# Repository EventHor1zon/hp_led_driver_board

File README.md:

# hp_led_driver_board
10W RGB LED Driver &amp;Controller board

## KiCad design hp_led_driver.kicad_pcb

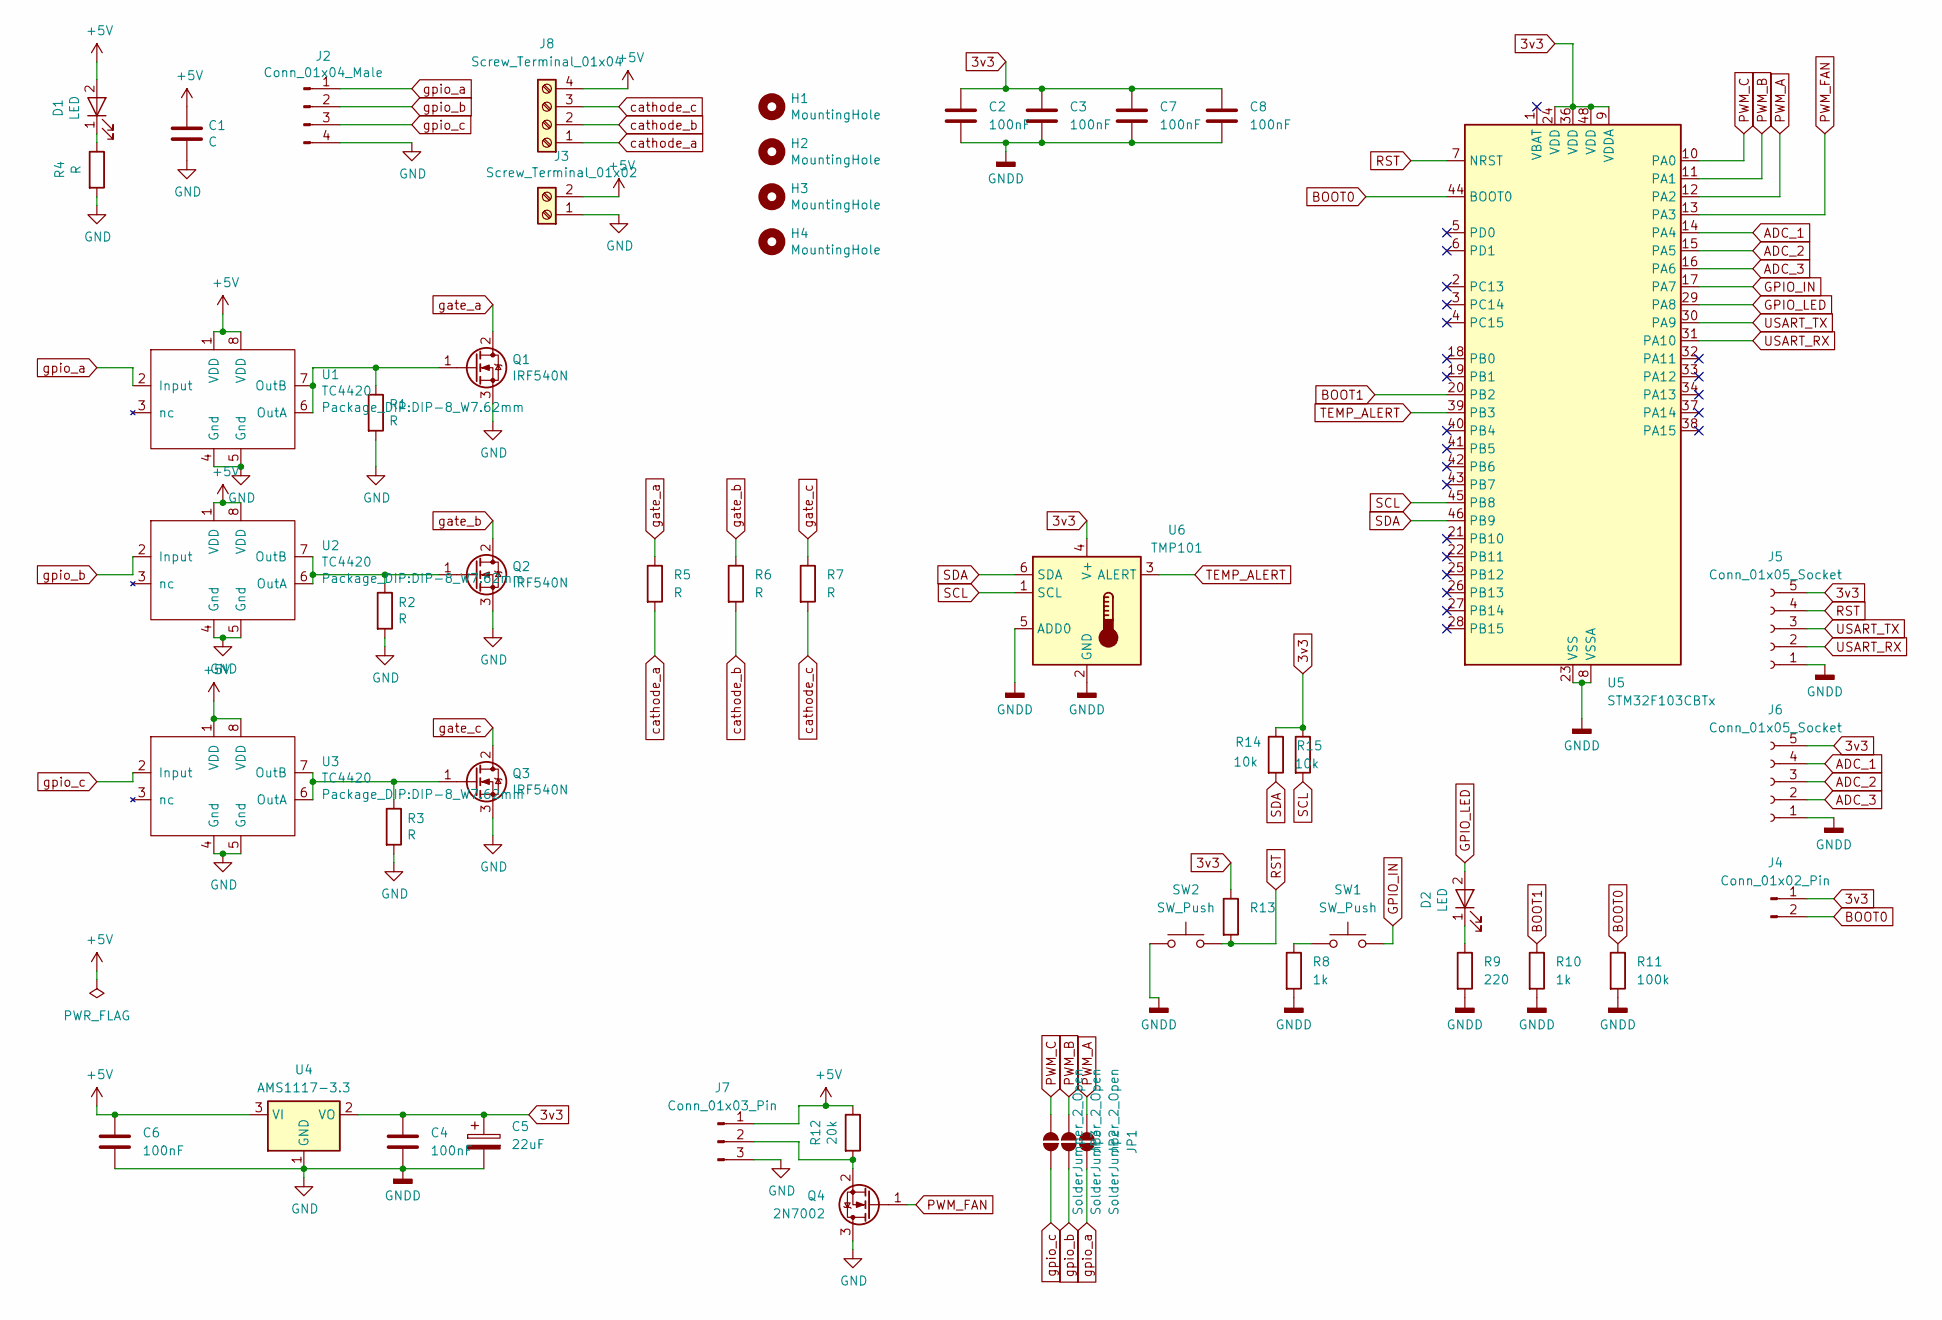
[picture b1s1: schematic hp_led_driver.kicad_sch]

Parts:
C1: C; CP_Radial_Tantal_D4.5mm_P2.50mm
C2, C3, C4, C6, C7, C8: 100nF; C_0805_2012Metric_Pad1.18x1.45mm_HandSolder
C5: 22uF; CP_Radial_Tantal_D4.5mm_P2.50mm
D1, D2: LED; LED_0805_2012Metric_Pad1.15x1.40mm_HandSolder
H1, H2, H3, H4: MountingHole; MountingHole_2.5mm_Pad
J2: Conn_01x04_Male; PinHeader_1x04_P2.54mm_Vertical
J3: Screw_Terminal_01x02; TerminalBlock_bornier-2_P5.08mm
J4: Conn_01x02_Pin; PinHeader_1x02_P2.54mm_Vertical
J5, J6: Conn_01x05_Socket; PinHeader_1x05_P2.54mm_Vertical
J7: Conn_01x03_Pin; PinHeader_1x03_P2.54mm_Vertical
J8: Screw_Terminal_01x04; TerminalBlock_bornier-4_P5.08mm
JP1, JP2, JP3: SolderJumper_2_Open; SolderJumper-2_P1.3mm_Open_TrianglePad1.0x1.5mm
Q1, Q2, Q3: IRF540N; TO-220-3_Vertical
Q4: 2N7002; SOT-23
R1, R2, R3: R; R_Axial_DIN0207_L6.3mm_D2.5mm_P7.62mm_Horizontal
R4: R; R_0805_2012Metric
R5, R6, R7: R; R_Axial_Power_L25.0mm_W6.4mm_P30.48mm
R8, R10: 1k; R_0805_2012Metric
R9: 220; R_0805_2012Metric
R11: 100k; R_0805_2012Metric
R12: 20k; R_0805_2012Metric
R13, R14, R15: 10k; R_0805_2012Metric
SW1, SW2: SW_Push; SW_PUSH_6mm
U1, U2, U3: TC4420; DIP-8_W7.62mm
U4: AMS1117-3.3; SOT-223-3_TabPin2
U5: STM32F103CBTx; LQFP-48_7x7mm_P0.5mm
U6: TMP101; SOT-23-6

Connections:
3v3: C2.1, C3.1, C4.1, C5.1, C7.1, C8.1, J4.1, J5.5, J6.5, R13.1, R14.1, R15.1, U4.2 (VO), U5.9 (VDDA), U5.24 (VDD), U5.36 (VDD), U5.48 (VDD), U6.4 (V+); also elsewhere on the board
+5V: C1.1, C6.1, D1.2 (A), J3.2, J7.1, J8.4, R12.1, U1.1 (VDD), U1.8 (VDD), U2.1 (VDD), U2.8 (VDD), U3.1 (VDD), U3.8 (VDD), U4.3 (VI)
ADC_1: J6.4, U5.14 (PA4)
ADC_2: J6.3, U5.15 (PA5)
ADC_3: J6.2, U5.16 (PA6)
BOOT0: J4.2, R11.1, U5.44 (BOOT0); also elsewhere on the board
BOOT1: R10.1, U5.20 (PB2)
GND: C1.2, C2.2, C3.2, C4.2, C5.2, C6.2, C7.2, C8.2, J2.4, J3.1, J5.1, J6.1, J7.3, Q1.3 (S), Q2.3 (S), Q3.3 (S), Q4.3 (D), R1.2, R2.2, R3.2, R4.2, R8.2, R9.2, R10.2, R11.2, SW2.1, U1.4 (Gnd), U1.5 (Gnd), U2.4 (Gnd), U2.5 (Gnd), U3.4 (Gnd), U3.5 (Gnd), U4.1 (GND), U5.8 (VSSA), U5.23 (VSS), U5.35 (VSS), U5.47 (VSS), U6.2 (GND), U6.5 (ADD0); also elsewhere on the board
GPIO_IN: SW1.2, U5.17 (PA7); also elsewhere on the board
GPIO_LED: D2.2 (A), U5.29 (PA8); also elsewhere on the board
unnamed: D1.1 (K), R4.1
unnamed 11: D2.1 (K), R9.1; also elsewhere on the board
unnamed: J7.2, Q4.2 (S), R12.2
unnamed: Q1.1 (G), R1.1, U1.6 (OutA), U1.7 (OutB)
unnamed: Q2.1 (G), R2.1, U2.6 (OutA), U2.7 (OutB)
unnamed: Q3.1 (G), R3.1, U3.6 (OutA), U3.7 (OutB)
unnamed 16: R8.1, SW1.1; also elsewhere on the board
PWM_A: JP1.1 (A), U5.12 (PA2)
PWM_B: JP2.1 (A), U5.11 (PA1)
PWM_C: JP3.1 (A), U5.10 (PA0)
PWM_FAN: Q4.1 (G), U5.13 (PA3)
RST: J5.4, R13.2, SW2.2, U5.7 (NRST); also elsewhere on the board
SCL: R15.2, U5.45 (PB8), U6.1 (SCL)
SDA: R14.2, U5.46 (PB9), U6.6 (SDA)
TEMP_ALERT: U5.39 (PB3), U6.3 (ALERT)
USART_RX: J5.2, U5.31 (PA10)
USART_TX: J5.3, U5.30 (PA9)
cathode_a: J8.1, R5.2
cathode_b: J8.2, R6.2
cathode_c: J8.3, R7.2
gate_a: Q1.2 (D), R5.1
gate_b: Q2.2 (D), R6.1
gate_c: Q3.2 (D), R7.1
gpio_a: J2.1, JP1.2 (B), U1.2 (Input)
gpio_b: J2.2, JP2.2 (B), U2.2 (Input)
gpio_c: J2.3, JP3.2 (B), U3.2 (Input)

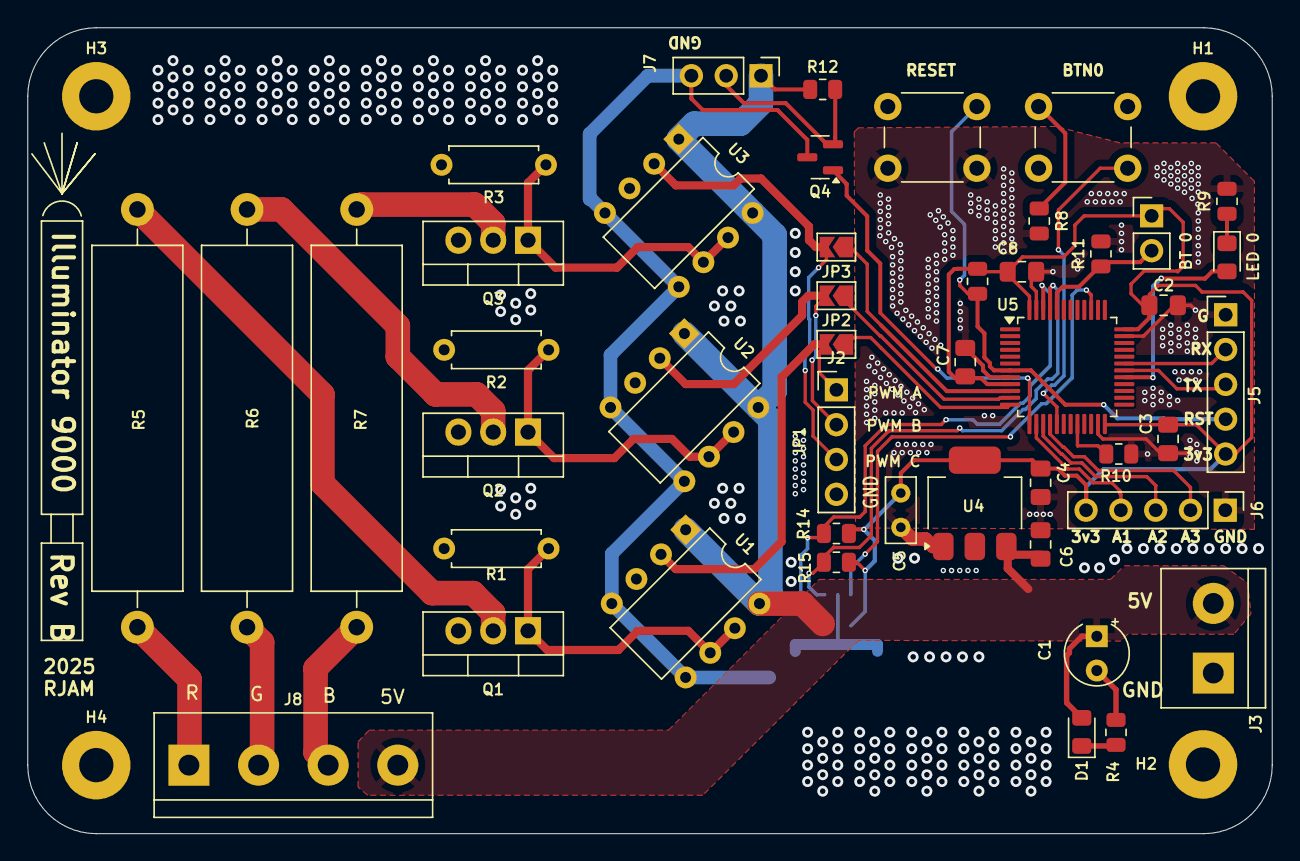
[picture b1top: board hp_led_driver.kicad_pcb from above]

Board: 2 copper layers, 90.8 x 58.8 mm, 51 parts (1 on the bottom side), 36 nets.

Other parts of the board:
BT 0: Conn_01x02_Pin; PinHeader_1x02_P2.54mm_Vertical
BTN0: SW_Push; SW_PUSH_6mm
LED 0: LED; LED_0805_2012Metric_Pad1.15x1.40mm_HandSolder
RESET: SW_Push; SW_PUSH_6mm

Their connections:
3v3: BT 0.1; also elsewhere on the board
BOOT0: BT 0.2; also elsewhere on the board
GND: RESET.1; also elsewhere on the board
GPIO_IN: BTN0.2; also elsewhere on the board
GPIO_LED: LED 0.2 (A); also elsewhere on the board
unnamed 11: LED 0.1 (K); also elsewhere on the board
unnamed 16: BTN0.1; also elsewhere on the board
RST: RESET.2; also elsewhere on the board

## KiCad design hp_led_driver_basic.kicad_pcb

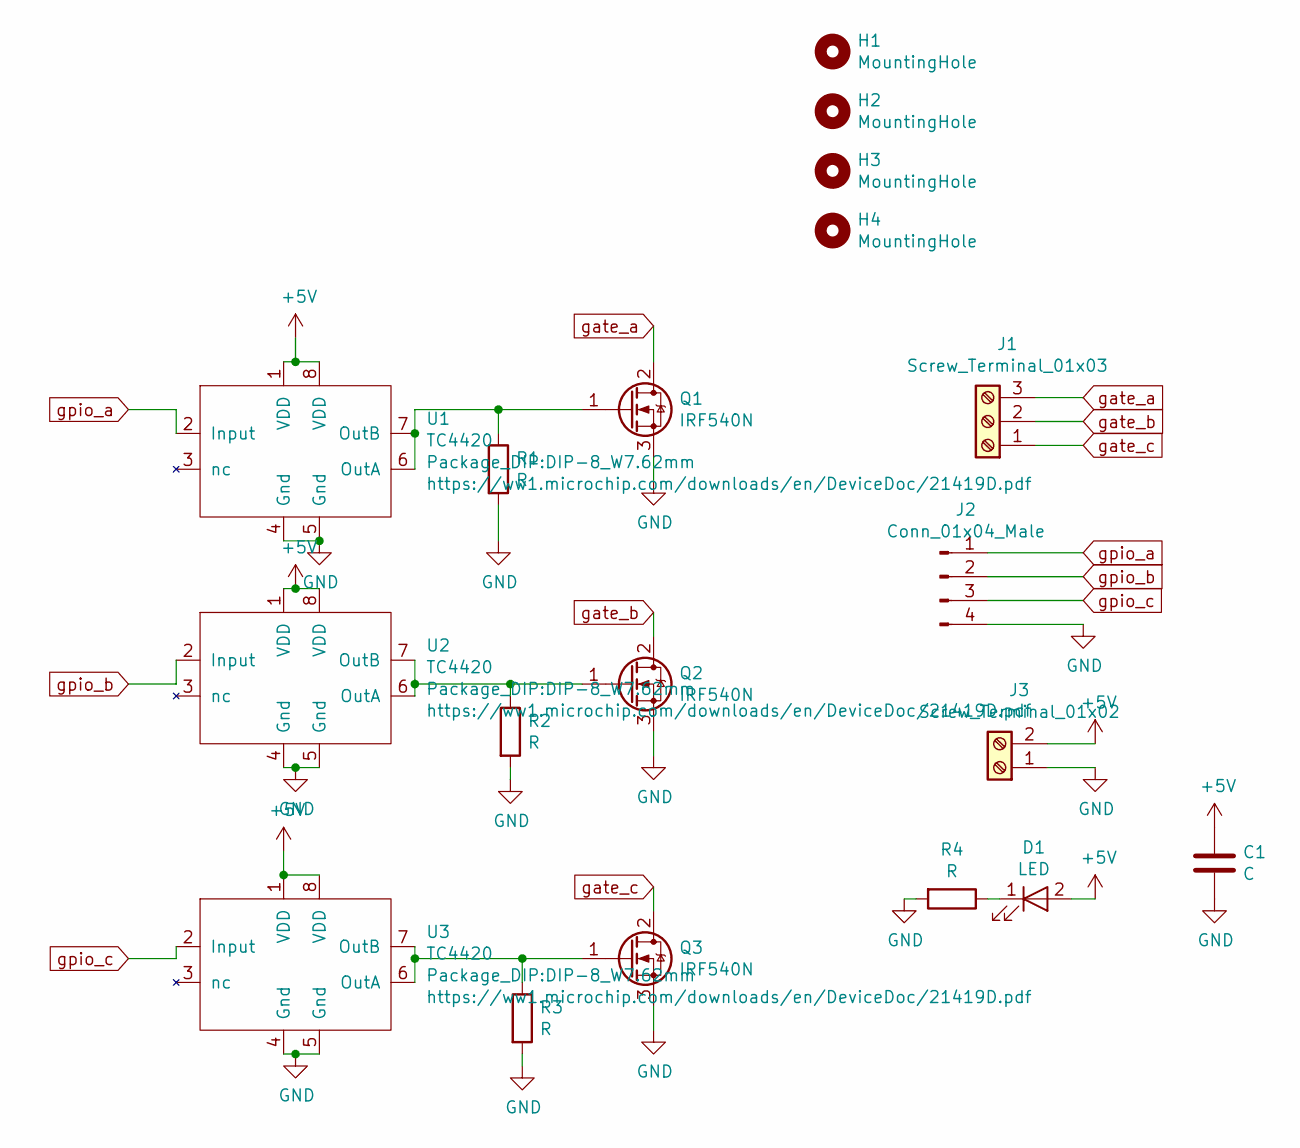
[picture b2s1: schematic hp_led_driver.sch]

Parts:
C1: C; C_Disc_D4.7mm_W2.5mm_P5.00mm
D1: LED; LED_1206_3216Metric
H1, H2, H3, H4: MountingHole; MountingHole_2.5mm_Pad
J1: Screw_Terminal_01x03; TerminalBlock_bornier-3_P5.08mm
J2: Conn_01x04_Male; PinHeader_1x04_P2.54mm_Vertical
J3: Screw_Terminal_01x02; TerminalBlock_bornier-2_P5.08mm
Q1, Q2, Q3: IRF540N; TO-220-3_Vertical
R1, R2, R3, R4: R; R_Axial_DIN0207_L6.3mm_D2.5mm_P7.62mm_Horizontal
U1, U2, U3: TC4420; DIP-8_W7.62mm

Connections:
+5V: C1.1, D1.2 (A), J3.2, U1.1 (VDD), U1.8 (VDD), U2.1 (VDD), U2.8 (VDD), U3.1 (VDD), U3.8 (VDD)
GND: C1.2, J2.4, J3.1, Q1.3 (S), Q2.3 (S), Q3.3 (S), R1.2, R2.2, R3.2, R4.2, U1.4 (Gnd), U1.5 (Gnd), U2.4 (Gnd), U2.5 (Gnd), U3.4 (Gnd), U3.5 (Gnd)
unnamed: D1.1 (K), R4.1
unnamed: Q1.1 (G), R1.1, U1.6 (OutA), U1.7 (OutB)
unnamed: Q2.1 (G), R2.1, U2.6 (OutA), U2.7 (OutB)
unnamed: Q3.1 (G), R3.1, U3.6 (OutA), U3.7 (OutB)
gate_a: J1.3, Q1.2 (D)
gate_b: J1.2, Q2.2 (D)
gate_c: J1.1, Q3.2 (D)
gpio_a: J2.1, U1.2 (Input)
gpio_b: J2.2, U2.2 (Input)
gpio_c: J2.3, U3.2 (Input)

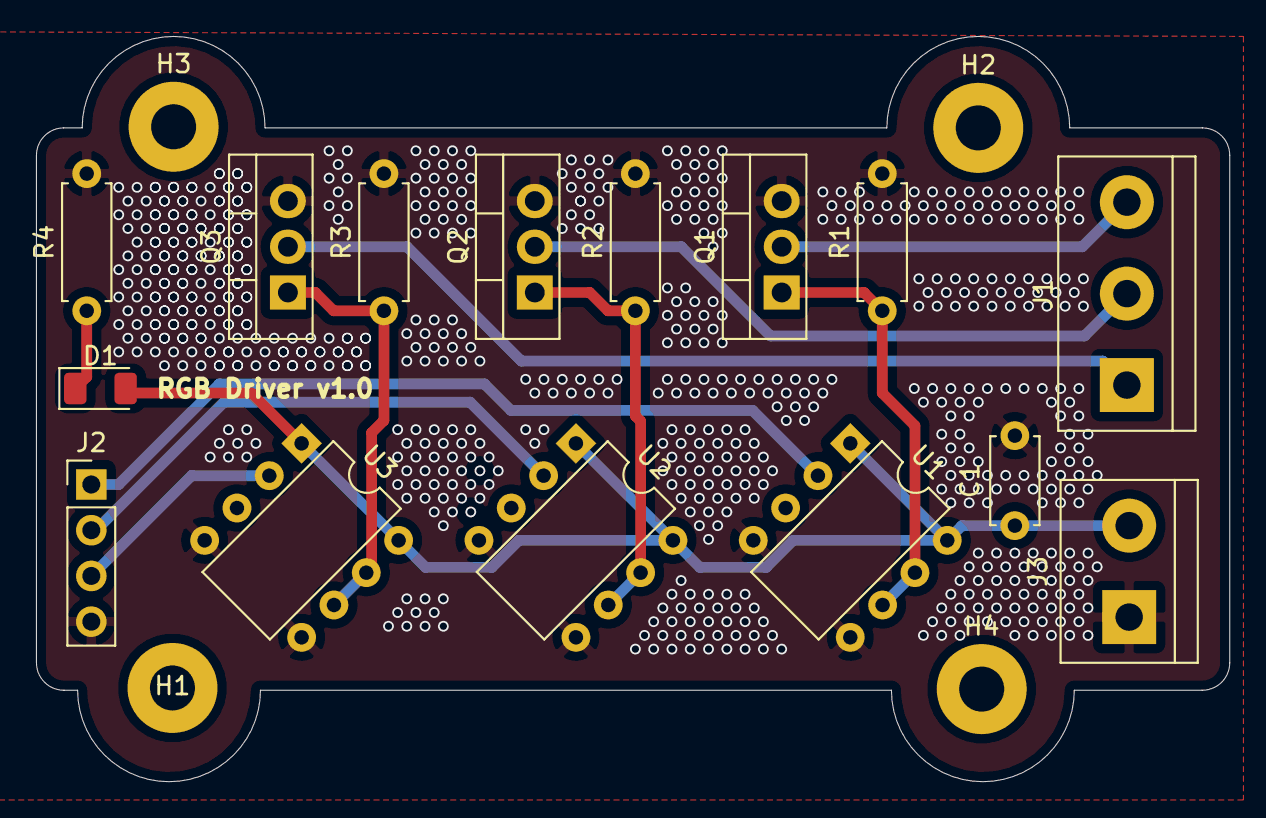
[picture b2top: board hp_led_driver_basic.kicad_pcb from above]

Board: 2 copper layers, 66.3 x 41.4 mm, 19 parts (0 on the bottom side), 12 nets.

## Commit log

2025-04-09 board files
